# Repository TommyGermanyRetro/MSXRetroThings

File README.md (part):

# MSXRetroThings
<i>Some nerdy hard- and software for MSX machines</i>

When I was a child, my first computer was a <a href="https://www.msx.org/wiki/Category:SVI-3x8">SV 318 MKII</a> with a cassette recorder. But neither SPECTRON nor ARMOURED ASSAULT were my favourites - the expansion port and the table of its pins in the manual caught my full interest.

Unfortunately, I had no real clue how to connect those signals to my Z80 PIO in a way that worked, so I lost the fun of playing around with the hardware.

Now, 40 years later, I got a <a href="https://www.msx.org/wiki/Spectravideo_SVI-728">SVI 728</a> and a <a href="https://www.ebay.de/sch/i.html?item=332817640567&rt=nc&_trksid=p4429486.m145687.l2562&_ssn=fractal2000">memory mapper / SD card cartridge</a> from the bay, and also a <a href="https://www.8bits4ever.net/product-page/sxe-msx2-fpga-computer">SX-E MSX2+</a>, and started over.

I had a lot of chips in my basket like Z80 PIO, 8255, 8254, SJA1000, PCF8584 etc. It started with MSX cartridges, ROM code and <a href="https://rc2014.co.uk/">RC2014 cards</a> - and then one thing led to another:

- a real application on top of it: an MSX that joins a Maerklin model railway CAN bus as an accessory module,
- tools to bring old Spectravideo SVI-318/328 software back to life and over to MSX,
- my own emulators for the machines I grew up with and the ones I own now,
- a USB board that runs real MSX cartridges inside an emulator on the PC,
- the MSX1 picture on a PC screen, and a slot expander for more cartridges than slots.

Everything here is retro and nerdy stuff for your own developments - or just for gaming.

Some of the software comes from KONAMIMAN, especially the UNAPI structure and the memory allocation in BASIC for working areas in RAM. Please have a look at his <a href="https://www.konamiman.com/msx/msx-e.html">git</a> for further information.

Have fun and stay healthy,

Thomas

## Contents

| | Topic | In short |
| --- | --- | --- |
| 1 | [XIO cartridge](#1-msxretrothings---the-xio-cartridge) | switched IO, 8259 interrupt controller, IM2 emulation |
| 2 | [RCX ROM cartridge and RC2014 cards](#2-msxretrothings---the-rcx-rom-cartridge-and-rc2014-cards) | BASIC/UNAPI driver ROM for I2C/RTC, PIO, 8255, 8254, CAN, SPI, A/D, D/A cards |
| 3 | [mbc89](#3-msxretrothings---mbc89-a-maerklin-connect6021-can-accessory-module) | Maerklin Connect6021 CAN accessory module as an MSX-DOS 2 program |
| 4 | [Tools](#4-msxretrothings---tools) | SVI-3x8 TXT/CAS converter, CP/M disk builder, game porter to MSX |
| 5 | [Emulators](#5-msxretrothings---emulators) | SVI-318, SVI-328, SVI-728 and Philips VG-8235 |
| 6 | [USB2SLOT](#6-msxretrothings---usb2slot-real-msx-cartridges-in-openmsx) | real MSX cartridges in openMSX and the emulators above |
| 7 | [TMS9918A](#7-msxretrothings---tms9918a-the-msx1-picture-on-the-pc-screen) | the MSX1 picture on the PC screen |
| 8 | [Slot expander](#8-msxretrothings---slot-expander-four-cartridge-slots-for-one-msx-slot) | four cartridge slots for one MSX slot |
| 9 | [License](#9-license) | |

## 1. MSXRetroThings - The XIO cartridge

#### <b>1.1 The XIO cartridge contains these functions:</b>

+ Switched IO based on the idea of ASCII to achive 256 additional IO locations
+ 8 channel programable interrupt controller 8259 with fallen edge sensitive inputs
+ 8 channel daisy chain IM2 emulator
+ BASIC and UNAPI commands to controll the functionallities of the cartridge in on board BIOS ROM

#### <b>1.2 Impressions:</b>

XIO cartridge used in a SX-E MSX2+ with adapter to RC2014 backplane

XIO cartridge

Boot message from BIOS ROM

#### <b>1.3 Hardware:</b>

The schematics of XIO is strictly build up in non smd method to enable people without special tools to rebuild the pcb. But it uses GAL chips for the switched IO decoder, the glue decoder for controll signals and the address decoder.

PCB files: Eagle schematics and layouts, Gerber and drill files (also as zip for the PCB maker) and bills of materials of the XIO cartridge in [xio/pcb](xio/pcb) and of the RC2014 adapter in [rcx/rc2014_adapter/pcb](rcx/rc2014_adapter/pcb); GAL equations in [xio/gal](xio/gal).

The XIO OUT/IN functions work without installing the XIO card. If the XIO card is installed correctly, the green LED shows that alle 16 interrupt channels are ready to use. A blinking yellow LED shows activities to the switched IO addresses. It signals, that the switched IO is selected via &H40 of the original MSX IO bus. The red LED shows a working supply.

#### <b>1.4 Software:</b>

The BIOS for the card functions is provided in the on board ROM (EEPROM). It contains the additional BASIC commands and an instance of UNAPI.

For SDCC developments, a library was created as bridge to the ROM.

Command reference (syntax, parameters, UNAPI numbers, SDCC functions): [xio/README.md](xio/README.md#command-reference)

[↑ Contents](#contents)

## 2. MSXRetroThings - The RCX ROM cartridge and RC2014 cards

#### <b>2.1 The RCX ROM cartridge contains these functions:</b>

+ Up to 16 RC2014 cards installable with used IO address control and 16 bytes of free RAM each card

+ BASIC, SDCC and UNAPI commands to controll the functions of the cartridge in separate BIOS ROM cartridge

+ SDCC and UNAPI commands to controll the functions of the cartridge also avaiable as Driver for MSX-DOS 2

+ [RC2014 card with PCF8584 I2C Controller (3 ports via Seeed) and PCF8583 battery buffered RTC](#a-rc2014-card-with-pcf8584-i2c-controller-3-ports-via-seeed-and-pcf8583-battery-buffered-rtc)

+ [RC2014 card with SJA1000 CAN controller (single use only)](#e-rc2014-card-with-sja1000-can-controller-single-use-only)

+ [RC2014 card with 8255A PIO](#c-rc2014-card-with-8255a-pio)

+ [RC2014 card with 8254A CTR](#d-rc2014-card-with-8254a-ctr)

+ [RC2014 card with 4x SPI bus up to 2 MHz via ATMEGA8](#f-rc2014-card-with-4x-spi-bus-up-to-2-mhz-via-atmega8)

+ [RC2014 card with ADS1220 4 channel 24 bit A/D converter via ATMEGA8](#g-rc2014-card-with-ads1220-4-channel-24-bit-ad-converter-via-atmega8)

+ [RC2014 card with MCP4822 4 channel 12 bit D/A converter via ATMEGA8](#i-rc2014-card-with-mcp4822-4-channel-12-bit-da-converter-via-atmega8)

+ [RC2014 card SC103 with Z80 PIO](#b-rc2014-card-sc103-with-z80-pio)

+ [RC2014 card SC725 with Z80 SIO and Z80 CTC](#h-rc2014-card-sc725-with-z80-sio-and-z80-ctc)

The schematics of RC2014 cards are strictly build up in non smd method to enable people without special tools to rebuild the pcb.

#### <b>2.2 Impressions:</b>

Slot ROM

Boot message from BIOS ROM

#### <b>2.3 Hardware:</b>

PCB files: Eagle schematic and layout, Gerber and drill files (also as zip for the PCB maker) and bill of materials in [rcx/rc2014_rom+ram/pcb](rcx/rc2014_rom+ram/pcb).

#### <b>2.4 Software:</b>

The BIOS for the card functions is provided in the on board ROM (EEPROM). It contains the additional BASIC commands and an instance of UNAPI.

As a software-only alternative to the physical ROM cartridge, [`RCXRAM.COM`](rcx/rc2014_rom+ram/drv/RCXRAM.COM) installs the same `RCX_INTERFACE` UNAPI driver into mapped RAM at runtime instead of requiring a burned EEPROM - useful for testing and development without the actual cartridge. It is UNAPI/EXTBIOS-only (no BASIC `CALL` support, since that relies on BASIC's own boot-time scan of ROM header slots, which does not apply to a RAM segment). Covers all card types A through G and I.

For SDCC developments, a library was created as bridge to the ROM/DRV.

Command reference (syntax, parameters, UNAPI numbers, SDCC functions): [rcx/README.md](rcx/README.md#command-reference)

## A) RC2014 card with PCF8584 I2C Controller (3 ports via Seeed) and PCF8583 battery buffered RTC:

This RC2014 card contains an I2C bus controller PCF8584 and a PCF8583 RTC buffered by battery. The interrupt pins of both chips can be assigned to one of the XIO PIC interrupt channels.
Up to 16 cards of this type are possible.

#### <b>A.1 Impressions:</b>

RC2014 card on backplane

RC2014 card on backplane with I2C LCD from Seeed

RC2014 card on backplane contacted via BASIC to get TIME and DATE

#### <b>A.2 Hardware:</b>

PCB files: Eagle schematic and layout, Gerber and drill files (also as zip for the PCB maker) and bill of materials in [rcx/rc2014_card_a/pcb](rcx/rc2014_card_a/pcb).

#### <b>A.3 Software:</b>

The BIOS for the card functions is provided in the RCX slot ROM. It contains the additional BASIC commands (`I2C INIT/WR/WRB/RD/RDB/RESET`, `SET/GET TIME/DATE`) and an instance of UNAPI, so the same functions are callable directly via UNAPI/EXTBIOS from a `.COM` program without the BASIC interpreter. Test software exists both as interactive BASIC programs and as `.COM` tools, including a variant that keeps the SEED I2C LCD updated on every PIC interrupt and one that stays resident in memory (MemMan TSR) to keep updating the display in the background.

Command reference (syntax, parameters, UNAPI numbers, SDCC functions): [rcx/rc2014_card_a/README.md](rcx/rc2014_card_a/README.md#command-reference)

[↑ 2.1](#21-the-rcx-rom-cartridge-contains-these-functions)

## B) RC2014 card SC103 with Z80 PIO

The original RC2014 card SC103 from Small Computer Central: Z80 PIO with two 8-bit bidirectional ports A and B, each with two handshake lines. Port mode 0 (output), 1 (input), 2 (bidirectional, port A only) and 3 (bit control) are set by a raw control word. The IO base address is selectable (multiple of 4, 0...252), so several cards can be used side by side. Interrupts use the PIO's own IM2 vector through an XIO Z80 interrupt channel (8...15), so the XIO cartridge is needed for interrupt operation only.

#### <b>B.1 Impressions:</b>

RC2014 card on backplane

#### <b>B.2 Hardware:</b>

Original SC103 kit from Small Computer Central, no own PCB. The base address is set with the 6-way DIP switch SW1 (switches 1...6 = 128, 64, 32, 16, 8, 4; the address is the sum of the switches in the Off position); the card uses the base address and the next three addresses. Recommended by the manufacturer: `&H68` (second card `&H6C`). The ports are on P2 (2x13 pins, ribbon cable) and P3 (1x29 pins, Dupont). JP1/JP2 open: IEI/IEO only on P4, IEI pulled high on the card. Details: [rcx/rc2014_card_b/README.md](rcx/rc2014_card_b/README.md#hardware-setup).

#### <b>B.3 Software:</b>

The BIOS for the card functions is provided in the RCX slot ROM. It contains the additional BASIC commands (`PIO INIT`, `PIO A/B RD/WR`, `PIO A/B CTRL`) and an instance of UNAPI, so the same functions are callable directly via UNAPI/EXTBIOS from a `.COM` program without the BASIC interpreter. `PIO A/B CTRL` passes the Z80 PIO control word unchanged (mode, direction, interrupt vector, interrupt mask). The first test program writes Port A in mode 0 and reads Port B in mode 1. The second runs Port B in mode 3 with PB0 as interrupt input: the PIO puts its own IM2 vector on the bus (channel 0...7 → vector = channel * 2), and a small Z80 service routine registered through `XIO SET ADDR` (XIO channel 8...15) reports which channel fired. Both tests exist in BASIC, as `.COM` (`/IO:`, `/INT:`) and in C/SDCC; the `.COM` and SDCC programs also run with the RAM driver `RCXRAM.COM`.

Command reference (syntax, parameters, UNAPI numbers, SDCC functions): [rcx/rc2014_card_b/README.md](rcx/rc2014_card_b/README.md#command-reference)

[↑ 2.1](#21-the-rcx-rom-cartridge-contains-these-functions)

## C) RC2014 card with 8255A PIO

RC2014 card with a 8255 PIO. Up to 16 cards are possible. The interrupt pins of PORT C can be assigned to one of the XIO PIC interrupt channels.

#### <b>C.1 Impressions:</b>

RC2014 card on backplane

#### <b>C.2 Hardware:</b>

PCB files: Eagle schematic and layout, Gerber and drill files (also as zip for the PCB maker) and bill of materials in [rcx/rc2014_card_c/pcb](rcx/rc2014_card_c/pcb).

#### <b>C.3 Software:</b>

The BIOS for the card functions is provided in the RCX slot ROM. It contains the additional BASIC commands (`PPI INIT`, `PPI A/B/C RD/WR`, `PPI CTRL`, `PPI SET/RESET`) and an instance of UNAPI, so the same functions are callable directly via UNAPI/EXTBIOS from a `.COM` program without the BASIC interpreter. A second test program runs Port B in Mode 1 (strobed input), where the 82C55 itself raises `INTR B` on PC0 - reported through XIO's standard interrupt handler, no custom service routine needed.

Command reference (syntax, parameters, UNAPI numbers, SDCC functions): [rcx/rc2014_card_c/README.md](rcx/rc2014_card_c/README.md#command-reference)

[↑ 2.1](#21-the-rcx-rom-cartridge-contains-these-functions)

## D) RC2014 card with 8254A CTR

RC2014 card with a 8254 CTR. Up to 16 cards are possible. The interrupt pins of TIMER 0 and 1 can be assigned to one of the XIO PIC interrupt channels. This module does not work with internal clock if 8253 (max. 1 MHz) is used.

#### <b>D.1 Impressions:</b>

RC2014 card on backplane

#### <b>D.2 Hardware:</b>

PCB files: Eagle schematic and layout, Gerber and drill files (also as zip for the PCB maker) and bill of materials in [rcx/rc2014_card_d/pcb](rcx/rc2014_card_d/pcb).

#### <b>D.3 Software:</b>

The BIOS for the card functions is provided in the RCX slot ROM. It contains the additional BASIC commands (`TIMER INIT`, `TIMER 0/1/2 RD/WR`, `TIMER CTRL`, `TIMER SET/RESET GATE`) and an instance of UNAPI, so the same functions are callable directly via UNAPI/EXTBIOS from a `.COM` program without the BASIC interpreter. A second test program wires one of the counter outputs to a PIC interrupt channel and keeps a running interrupt count on screen.

Command reference (syntax, parameters, UNAPI numbers, SDCC functions): [rcx/rc2014_card_d/README.md](rcx/rc2014_card_d/README.md#command-reference)

[↑ 2.1](#21-the-rcx-rom-cartridge-contains-these-functions)

## E) RC2014 card with SJA1000 CAN controller (single use only)

RC2014 card with SJA1000 CAN controller and RJ45 sockets with automatic termination function. The software provides PELICAN Mode and 250 kBit/s.

Only one card is possible due to RAM allocation and interrupt handling. The interrupt pin of the SJA1000 can be assigned to one of the XIO PIC interrupt channels.

#### <b>E.1 Impressions:</b>

RC2014 card on backplane

#### <b>E.2 Hardware:</b>

PCB files: Eagle schematic and layout, Gerber and drill files (also as zip for the PCB maker) and bill of materials in [rcx/rc2014_card_e/pcb](rcx/rc2014_card_e/pcb).

#### <b>E.3 Software:</b>

The BIOS for the card functions is provided in the RCX slot ROM. It contains the additional BASIC commands (`CAN INIT`, `CAN WR/RD`, `CAN CHECK/RX/TX`, `CAN GET ADDR`) and an instance of UNAPI, so the same functions are callable directly via UNAPI/EXTBIOS from a `.COM` program without the BASIC interpreter. The test program receives and sends CAN messages interrupt-driven, e.g. for a Maerklin CS3 bus, by registering the ROM's own CAN service routine (returned by `CAN GET ADDR`) directly through `XIO SET ADDR` - no custom interrupt code needed.

Command reference (syntax, parameters, UNAPI numbers, SDCC functions): [rcx/rc2014_card_e/README.md](rcx/rc2014_card_e/README.md#command-reference)

[↑ 2.1](#21-the-rcx-rom-cartridge-contains-these-functions)

## F) RC2014 card with 4x SPI bus up to 2 MHz via ATMEGA8

RC2014 card with 4 SPI busses selectable via software with baudrate up to 2 MHz. Up to 16 SPI cards are possible. The interrupt pin of the ATMEGA8 can be assigned to one of the XIO PIC interrupt channels.

#### <b>F.1 Impressions:</b>

RC2014 card on backplane

#### <b>F.2 Hardware:</b>

PCB files: Eagle schematic and layout, Gerber and drill files (also as zip for the PCB maker) and bill of materials in [rcx/rc2014_card_f/pcb](rcx/rc2014_card_f/pcb).

#### <b>F.3 Software:</b>

The BIOS for the card functions is provided in the RCX slot ROM. It contains the additional BASIC commands (`SPI INIT/MODE`, `SPI WR/WRB/RD/RDB/RDH`) and an instance of UNAPI, so the same functions are callable directly via UNAPI/EXTBIOS from a `.COM` program without the BASIC interpreter. Up to 4 independent SPI busses are addressable per card; the test program exercises a MCP23S17 GPIO expander as a Port A/B loopback test.

Command reference (syntax, parameters, UNAPI numbers, SDCC functions): [rcx/rc2014_card_f/README.md](rcx/rc2014_card_f/README.md#command-reference)

[↑ 2.1](#21-the-rcx-rom-cartridge-contains-these-functions)

## G) RC2014 card with ADS1220 4 channel 24 bit A/D converter via ATMEGA8

RC2014 card with ADS1220 module. Up to 16 cards are possible. The interrupt pin of ATMEGA8 can be assigned to one of the XIO PIC interrupt channels.

#### <b>G.1 Impressions:</b>

RC2014 card on backplane

#### <b>G.2 Hardware:</b>

PCB files: Eagle schematic and layout, Gerber and drill files (also as zip for the PCB maker) and bill of materials in [rcx/rc2014_card_g/pcb](rcx/rc2014_card_g/pcb).

#### <b>G.3 Software:</b>

The BIOS for the card functions is provided in the RCX slot ROM. It contains the additional BASIC commands (`ADS INIT/MODE/CMD/STATUS/READ/GET`) and an instance of UNAPI, so the same functions are callable directly via UNAPI/EXTBIOS from a `.COM` program without the BASIC interpreter. `ADS GET` automates the whole measurement sequence (set MODE, start conversion, select channel, read all 4 RESULT bytes) into a single native `SNG` float value.

Command reference (syntax, parameters, UNAPI numbers, SDCC functions): [rcx/rc2014_card_g/README.md](rcx/rc2014_card_g/README.md#command-reference)

[↑ 2.1](#21-the-rcx-rom-cartridge-contains-these-functions)

## H) RC2014 card SC725 with Z80 SIO and Z80 CTC

The original RC2014 card SC725 from Small Computer Central as MSX COM port: Z80 SIO/2 with two serial ports, Z80 CTC as baud rate generator (110...19200 baud from the MSX bus clock). Port A and B become `COM0:` and `COM1:`. Interrupt driven receiving through the XIO Z80 interrupt channel 12, so the XIO cartridge is needed.

#### <b>H.1 Impressions:</b>

RC2014 card on backplane

#### <b>H.2 Hardware:</b>

Original SC725 kit from Small Computer Central, no own PCB. Jumpers for the MSX bus clock: JP4 1-2 (CTC clock = bus CLK), JP5 5-6 and JP6 5-6 (SIO A/B clock = CTC channel 0/1), JP1/JP2/JP3 open. Fixed IO addresses `&H80`...`&H83` (SIO) and `&H88`...`&H8B` (CTC). Details: [rcx/rc2014_card_h/README.md](rcx/rc2014_card_h/README.md#hardware-setup).

#### <b>H.3 Software:</b>

The BIOS for the card functions is provided in the RCX slot ROM. It contains an MSX RS-232C driver following the "RS-232C Extended BIOS Call Specification" (EXTBIO device 8, multi channel type), so any RS-232C aware MSX program finds the port. BASIC gets `_COM INIT`, the devices `COM0:`/`COM1:` (`OPEN`, `PRINT #`, `INPUT$`, `LOC`, `LOF`, `EOF`) and the CALL statements `COMINI`, `COMDTR`, `COMSTAT` and `COMBREAK`. CTS-RTS handshake, XON/XOFF, auto LF, SI/SO and break are supported. `.COM` and SDCC programs use the same driver via UNAPI/EXTBIOS, also with the RAM driver `RCXRAM.COM`.

Command reference (syntax, parameters, UNAPI numbers, SDCC functions): [rcx/rc2014_card_h/README.md](rcx/rc2014_card_h/README.md#command-reference)

[↑ 2.1](#21-the-rcx-rom-cartridge-contains-these-functions)

[↑ Contents](#contents)

## I) RC2014 card with MCP4822 4 channel 12 bit D/A converter via ATMEGA8

RC2014 card with 2x MCP4822. Up to 16 cards are possible. The interrupt pin of ATMEGA8 can be assigned to one of the XIO PIC interrupt channels.

#### <b>I.1 Impressions:</b>

RC2014 card on backplane

#### <b>I.2 Hardware:</b>

PCB files: Eagle schematic and layout, Gerber and drill files (also as zip for the PCB maker) and bill of materials in [rcx/rc2014_card_i/pcb](rcx/rc2014_card_i/pcb).

#### <b>I.3 Software:</b>

The BIOS for the card functions is provided in the RCX slot ROM. It contains the additional BASIC commands (`DAC INIT/SET/HOLD/CONF/GET`) and an instance of UNAPI, so the same functions are callable directly via UNAPI/EXTBIOS from a `.COM` program without the BASIC interpreter. Four outputs 0...4.095 V with 1 mV resolution; `DAC HOLD` and `DAC SET` together change several outputs at exactly the same moment.

Command reference (syntax, parameters, UNAPI numbers, SDCC functions): [rcx/rc2014_card_i/README.md](rcx/rc2014_card_i/README.md#command-reference)

[↑ 2.1](#21-the-rcx-rom-cartridge-contains-these-functions)

[↑ Contents](#contents)

## 3. MSXRetroThings - mbc89, a Maerklin Connect6021 CAN accessory module

#### <b>3.1 mbc89 provides:</b>

+ A full MSX-DOS 2 port of `mbc89`, one of the MBCAN family of Maerklin CS2/CS3 CAN-bus accessory modules - runs as a normal `.COM` program instead of the original's ATmega firmware

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
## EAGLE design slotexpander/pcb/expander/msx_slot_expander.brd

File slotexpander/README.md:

# Slot expander - four cartridge slots for one MSX slot

A slot expander for MSX computers: four cartridge slots behind one primary slot, as subslots 0-3 of
a standard MSX slot expander with its register at FFFFh. It sits outside the computer on a 50-wire
ribbon cable and has its own 5 V supply, so the cartridges in it do not load the power supply of the
MSX.

The expander connects to the MSX in one of two ways:

- **Spectravideo SVI-728:** the 50-pin box header of the expander follows the pinout of the
  SVI-728, so the ribbon cable goes straight to the SVI-728.
- **Any other MSX:** plug the Slot2Bus adapter into a cartridge slot. It takes the 50 contacts of
  the slot 1:1 to its box header, and the ribbon cable goes from there to the expander.

Tested on a Spectravideo SVI-728.

## Contents of this folder

| Path | Content |
| --- | --- |
| [pcb/expander](pcb/expander) | Eagle project of the expander: schematic `msx_slot_expander.sch`, layout `msx_slot_expander.brd`; bill of materials `msx_slot_expander_bom.csv` |
| [pcb/expander/gerber](pcb/expander/gerber) | Gerber RS-274X and Excellon drill files of the two-layer board, also as `msx_slot_expander_gerber.zip` for the PCB maker |
| [pcb/adapter](pcb/adapter) | Eagle project of the Slot2Bus adapter: `msx_slot2bus_expander.sch`, `msx_slot2bus_expander.brd`; bill of materials `msx_slot2bus_expander_bom.csv` |
| [pcb/adapter/gerber](pcb/adapter/gerber) | Gerber and drill files of the adapter, also as `msx_slot2bus_expander_gerber.zip` |
| [gal](gal) | GAL equations (WinCUPL) and programming files: `FPGA_EXP_ADR_BANKING` (GAL22V10), `FPGA_EXP_IO_CTRL` (GAL16V8) |
| [case](case) | 3D-printable enclosures as FreeCAD files: expander `MSX_EXPANDER_BOTTOM/TOP.FCStd`, adapter `MSX_CARD_SLOT2BUS_BOTTOM/TOP.FCStd` |
| [media](media) | Photo |

## 1. How it works

| Function | Implementation |
| --- | --- |
| Subslot register FFFFh | Two 74HCT30 detect the address FFFFh. The GAL22V10 `FPGA_EXP_ADR_BANKING` stores the value written to FFFFh while the slot is selected and returns it inverted on a read, as the MSX standard requires. |
| Subslot select | For each memory access, the GAL22V10 picks the two register bits of the page given by A15/A14. The GAL16V8 `FPGA_EXP_IO_CTRL` turns them into /SLTSL of subslot 0-3; accesses to FFFFh itself do not select a subslot. |
| Subslots on and off | DIP switch S101 connects each subslot select to its slot. Open, the subslot stays empty for the MSX. |
| /INT and /BUSDIR | Each slot reaches the line of the MSX through a diode, with a pull-up on the expander. |
| Sound | The sound output of each slot goes through its own 10 kOhm trimmer to the sound input of the MSX, so the level of each cartridge can be set. |
| Power | 5 V through a USB type B socket, a ferrite bead and the power switch; +12 V and -12 V for the slots from a DC-DC converter NMA0512. The 5 V of the MSX only light the LED "MSX". |

| LED | Meaning |
| --- | --- |
| MSX | the MSX is switched on (5 V on the ribbon cable) |
| EXP | the expander is switched on |

## 2. Hardware

- Order the boards with the zip files in `pcb/expander/gerber` and `pcb/adapter/gerber`. Check the
  layers in a Gerber viewer (for example the online viewer of the PCB maker) before you order. The
  parts are listed in the two bill-of-materials files.
- Program the GALs with `gal/FPGA_EXP_ADR_BANKING.jed` (GAL22V10) and `gal/FPGA_EXP_IO_CTRL.jed`
  (GAL16V8).
- The two LEDs have no series resistor on the board; use LEDs with a built-in resistor for 5 V.
- The ribbon cable has 50 wires with an IDC socket at each end. Mind pin 1 at both ends.
- Supply: a USB power supply with 5 V and enough current for the cartridges plugged in. The
  cartridges are powered by the expander, not by the MSX: with the expander switched off, they do not
  work.
- Switch on the expander first, then the MSX.
- No hot plug, just like a real MSX: change cartridges only with the expander and the MSX switched
  off.

## 3. Enclosures

`case` holds two-part enclosures as FreeCAD files, built with FreeCAD 1.0 (PartDesign):

| Files | Part | Size (outside) |
| --- | --- | --- |
| `MSX_EXPANDER_BOTTOM.FCStd`, `MSX_EXPANDER_TOP.FCStd` | expander | 150 x 115 mm; bottom part 10 mm, top part 30 mm high |
| `MSX_CARD_SLOT2BUS_BOTTOM.FCStd`, `MSX_CARD_SLOT2BUS_TOP.FCStd` | Slot2Bus adapter, cartridge shaped | 111 x 68 mm; bottom part 11 mm, top part 15 mm high |

Only the design files are included, no STL or G-code, so the enclosures can be adapted before
printing:

1. Open the files in FreeCAD 1.0 or newer and change the sketches as needed; the following features
   update automatically.
2. Select the body and export it as STL or 3MF (File > Export).
3. Slice the file for your printer as usual.

## 4. License

The parts in this folder follow the [license of this repository](../README.md#9-license): the
boards, the GAL equations and the enclosures CERN-OHL-S-2.0, documentation and photo CC BY-SA 4.0.

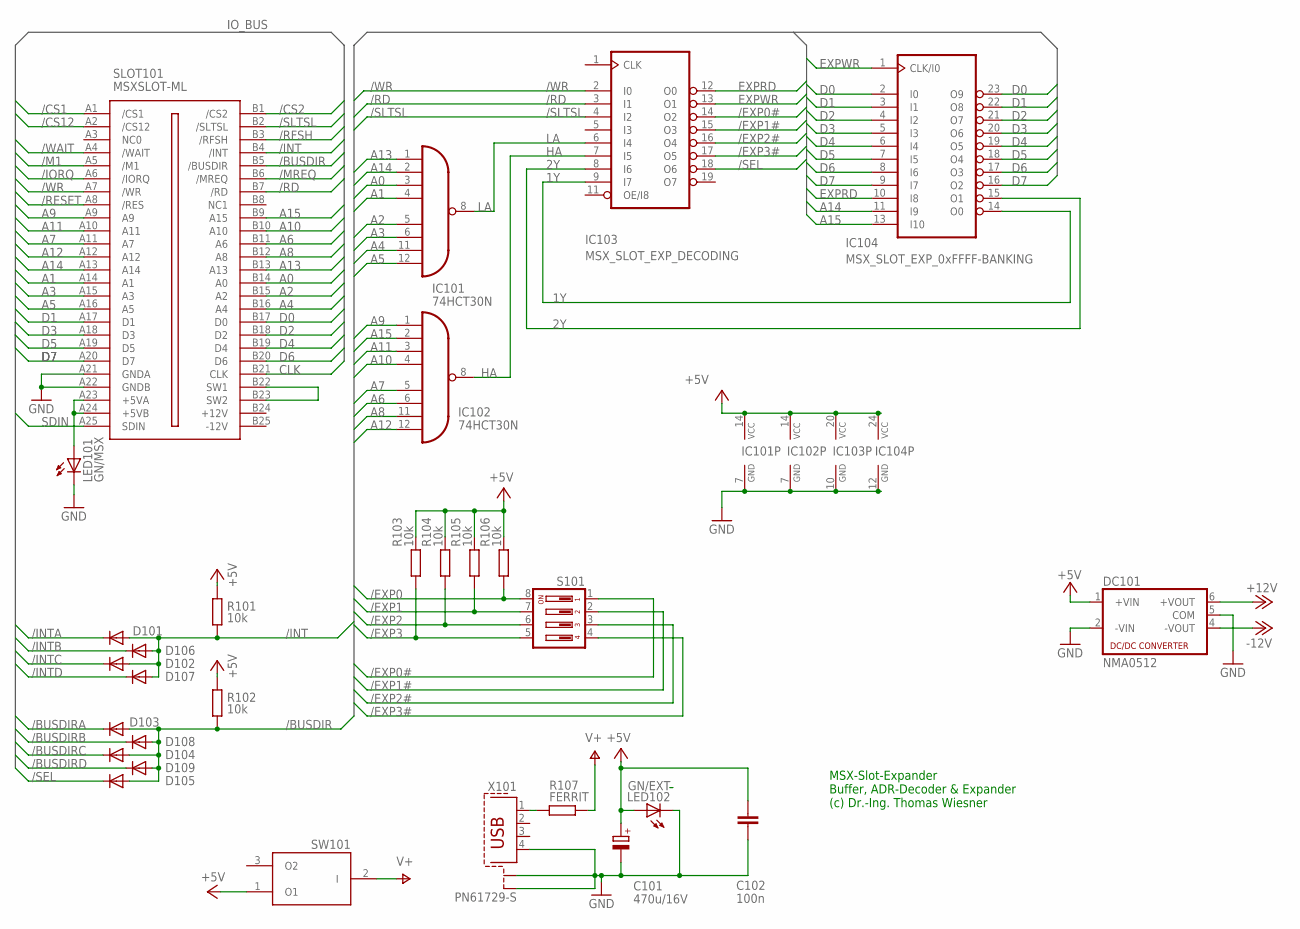
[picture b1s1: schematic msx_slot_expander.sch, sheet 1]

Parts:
C101: 470u/16V; E3,5-8
C102: 100n; C025-025X050
D101, D102, D103, D104, D105, D106, D107, D108, D109: 1N4148; DO35-10
DC101: NMA0512; NMA
IC101, IC102: 74HCT30N; DIL14
IC103: MSX_SLOT_EXP_DECODING; DIL20
IC104: MSX_SLOT_EXP_0xFFFF-BANKING; DIL24-3
LED101: GN/MSX; LED3MM
LED102: GN/EXT; LED3MM
R101, R102, R103, R104, R105, R106: 10k; 0207/10
R107: FERRIT; 0207/10
S101: DA04; DA-04
SLOT101: MSXSLOT-ML
SW101: TS-13PA; TS-13-P
X101: PN61729-S

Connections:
1Y: IC103.9 (I7), IC104.14 (O0)
2Y: IC103.8 (I6), IC104.15 (O1)
+5V: C101.+, C102.2, DC101.1 (+VIN), IC101.14 (VCC), IC102.14 (VCC), IC103.20 (VCC), IC104.24 (VCC), LED102.A, R101.2, R102.1, R103.2, R104.2, R105.2, R106.2, SW101.1 (O1); also elsewhere on the board
+12V: DC101.6 (+VOUT); also elsewhere on the board
-12V: DC101.4 (-VOUT); also elsewhere on the board
/BUSDIR: D103.A, D104.A, D105.A, D108.A, D109.A, R102.2, SLOT101.B5 (/BUSDIR)
/BUSDIRA: D103.C; also elsewhere on the board
/BUSDIRB: D108.C; also elsewhere on the board
/BUSDIRC: D104.C; also elsewhere on the board
/BUSDIRD: D109.C; also elsewhere on the board
/CS1: SLOT101.A1 (/CS1); also elsewhere on the board
/CS2: SLOT101.B1 (/CS2); also elsewhere on the board
/CS12: SLOT101.A2 (/CS12); also elsewhere on the board
/EXP0: R106.1, S101.8; also elsewhere on the board
/EXP0#: IC103.14 (O2), S101.1
/EXP1: R105.1, S101.7; also elsewhere on the board
/EXP1#: IC103.15 (O3), S101.2
/EXP2: R104.1, S101.6; also elsewhere on the board
/EXP2#: IC103.16 (O4), S101.3
/EXP3: R103.1, S101.5; also elsewhere on the board
/EXP3#: IC103.17 (O5), S101.4
/INT: D101.A, D102.A, D106.A, D107.A, R101.1, SLOT101.B4 (/INT)
/INTA: D101.C; also elsewhere on the board
/INTB: D106.C; also elsewhere on the board
/INTC: D102.C; also elsewhere on the board
/INTD: D107.C; also elsewhere on the board
/IORQ: SLOT101.A6 (/IORQ); also elsewhere on the board
/M1: SLOT101.A5 (/M1); also elsewhere on the board
/MREQ: SLOT101.B6 (/MREQ); also elsewhere on the board
/RD: IC103.3 (I1), SLOT101.B7 (/RD); also elsewhere on the board
/RESET: SLOT101.A8 (/RES); also elsewhere on the board
/RFSH: SLOT101.B3 (/RFSH); also elsewhere on the board
/SEL: D105.C, IC103.18 (O6)
/SLTSL: IC103.4 (I2), SLOT101.B2 (/SLTSL)
/WAIT: SLOT101.A4 (/WAIT); also elsewhere on the board
/WR: IC103.2 (I0), SLOT101.A7 (/WR); also elsewhere on the board
A0: IC101.3 (I2), SLOT101.B14 (A0); also elsewhere on the board
A1: IC101.4 (I3), SLOT101.A14 (A1); also elsewhere on the board
A2: IC101.5 (I4), SLOT101.B15 (A2); also elsewhere on the board
A3: IC101.6 (I5), SLOT101.A15 (A3); also elsewhere on the board
A4: IC101.11 (I6), SLOT101.B16 (A4); also elsewhere on the board
A5: IC101.12 (I7), SLOT101.A16 (A5); also elsewhere on the board
A6: IC102.6 (I5), SLOT101.B11 (A6); also elsewhere on the board
A7: IC102.5 (I4), SLOT101.A11 (A7); also elsewhere on the board
A8: IC102.11 (I6), SLOT101.B12 (A8); also elsewhere on the board
A9: IC102.1 (I0), SLOT101.A9; also elsewhere on the board
A10: IC102.4 (I3), SLOT101.B10 (A10); also elsewhere on the board
A11: IC102.3 (I2), SLOT101.A10 (A11); also elsewhere on the board
A12: IC102.12 (I7), SLOT101.A12; also elsewhere on the board
A13: IC101.1 (I0), SLOT101.B13 (A13); also elsewhere on the board
A14: IC101.2 (I1), IC104.11 (I9), SLOT101.A13 (A14); also elsewhere on the board
A15: IC102.2 (I1), IC104.13 (I10), SLOT101.B9 (A15); also elsewhere on the board
CLK: SLOT101.B21 (CLK); also elsewhere on the board
D0: IC104.2 (I0), IC104.23 (O9), SLOT101.B17 (D0); also elsewhere on the board
D1: IC104.3 (I1), IC104.22 (O8), SLOT101.A17 (D1); also elsewhere on the board
D2: IC104.4 (I2), IC104.21 (O7), SLOT101.B18 (D2); also elsewhere on the board
D3: IC104.5 (I3), IC104.20 (O6), SLOT101.A18 (D3); also elsewhere on the board
D4: IC104.6 (I4), IC104.19 (O5), SLOT101.B19 (D4); also elsewhere on the board
D5: IC104.7 (I5), IC104.18 (O4), SLOT101.A19 (D5); also elsewhere on the board
D6: IC104.8 (I6), IC104.17 (O3), SLOT101.B20 (D6); also elsewhere on the board
D7: IC104.9 (I7), IC104.16 (O2), SLOT101.A20 (D7); also elsewhere on the board
EXPRD: IC103.12 (O0), IC104.10 (I8)
EXPWR: IC103.13 (O1), IC104.1 (CLK/I0)
GND: C101.-, C102.1, DC101.2 (-VIN), DC101.5 (COM), IC101.7 (GND), IC102.7 (GND), IC103.10 (GND), IC104.12 (GND), LED101.K (C), LED102.K (C), SLOT101.A21 (GNDA), SLOT101.A22 (GNDB), X101.4, X101.S1, X101.S2; also elsewhere on the board
HA: IC102.8 (O), IC103.7 (I5)
LA: IC101.8 (O), IC103.6 (I4)
unnamed: LED101.A, SLOT101.A23 (+5VA), SLOT101.A24 (+5VB)
unnamed: R107.2, X101.1
unnamed: SLOT101.B22 (SW1), SLOT101.B23 (SW2)
SDIN: SLOT101.A25 (SDIN); also elsewhere on the board
V+: R107.1, SW101.2 (I)

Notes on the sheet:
MSX-Slot-Expander Buffer, ADR-Decoder & Expander (c) Dr.-Ing. Thomas Wiesner

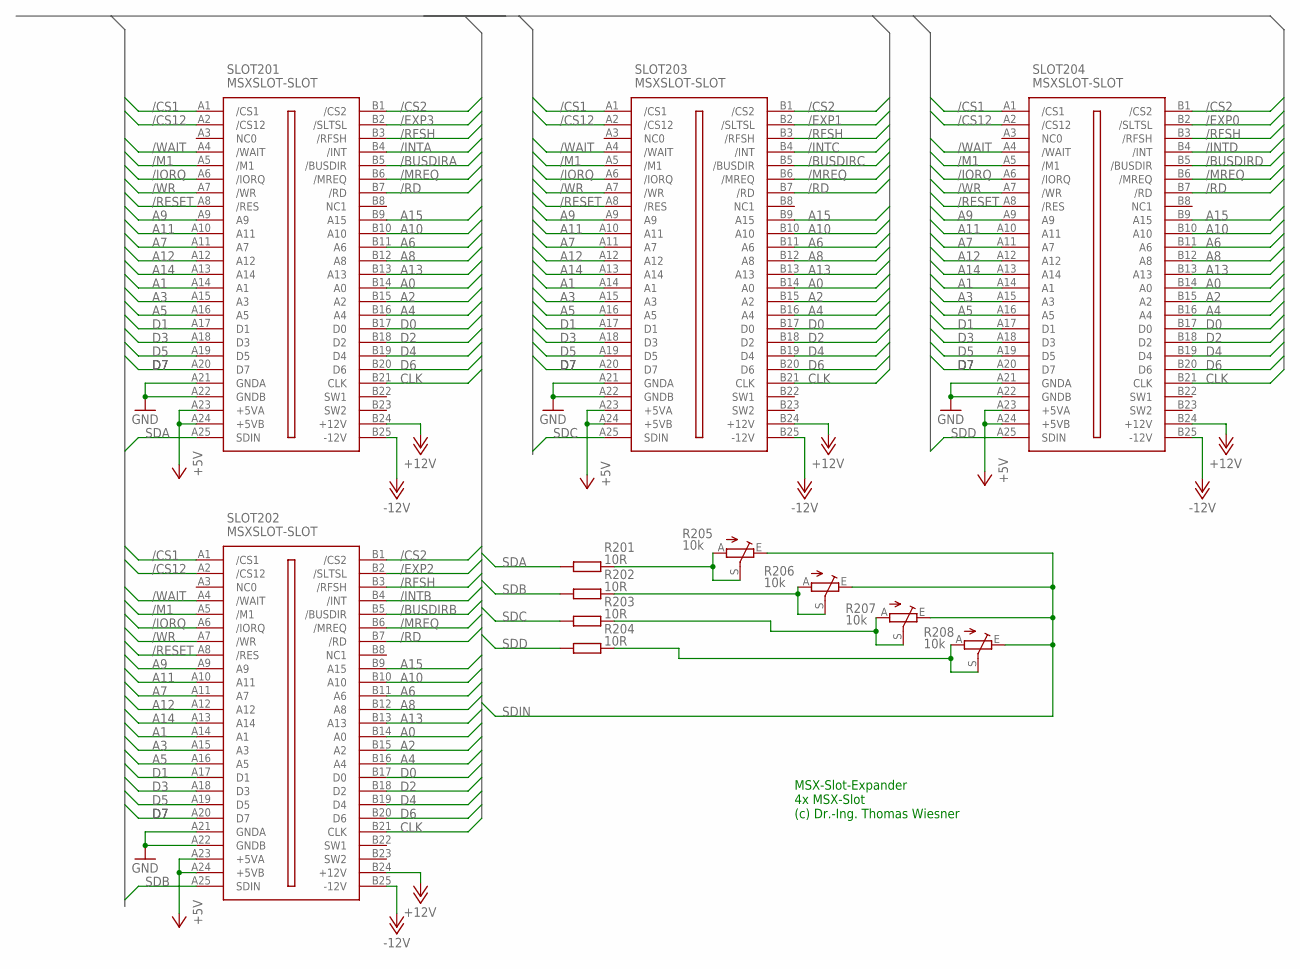
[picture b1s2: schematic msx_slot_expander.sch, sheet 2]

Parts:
R201, R202, R203, R204: 10R; 0207/10
R205, R206, R207, R208: 10k; SP19L
SLOT201, SLOT202, SLOT203, SLOT204: MSXSLOT-SLOT; MSXSLOT

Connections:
+5V: SLOT201.A23 (+5VA), SLOT201.A24 (+5VB), SLOT202.A23 (+5VA), SLOT202.A24 (+5VB), SLOT203.A23 (+5VA), SLOT203.A24 (+5VB), SLOT204.A23 (+5VA), SLOT204.A24 (+5VB); also elsewhere on the board
+12V: SLOT201.B24 (+12V), SLOT202.B24 (+12V), SLOT203.B24 (+12V), SLOT204.B24 (+12V); also elsewhere on the board
-12V: SLOT201.B25 (-12V), SLOT202.B25 (-12V), SLOT203.B25 (-12V), SLOT204.B25 (-12V); also elsewhere on the board
/BUSDIRA: SLOT201.B5 (/BUSDIR); also elsewhere on the board
/BUSDIRB: SLOT202.B5 (/BUSDIR); also elsewhere on the board
/BUSDIRC: SLOT203.B5 (/BUSDIR); also elsewhere on the board
/BUSDIRD: SLOT204.B5 (/BUSDIR); also elsewhere on the board
/CS1: SLOT201.A1 (/CS1), SLOT202.A1 (/CS1), SLOT203.A1 (/CS1), SLOT204.A1 (/CS1); also elsewhere on the board
/CS2: SLOT201.B1 (/CS2), SLOT202.B1 (/CS2), SLOT203.B1 (/CS2), SLOT204.B1 (/CS2); also elsewhere on the board
/CS12: SLOT201.A2 (/CS12), SLOT202.A2 (/CS12), SLOT203.A2 (/CS12), SLOT204.A2 (/CS12); also elsewhere on the board
/EXP0: SLOT204.B2 (/SLTSL); also elsewhere on the board
/EXP1: SLOT203.B2 (/SLTSL); also elsewhere on the board
/EXP2: SLOT202.B2 (/SLTSL); also elsewhere on the board
/EXP3: SLOT201.B2 (/SLTSL); also elsewhere on the board
/INTA: SLOT201.B4 (/INT); also elsewhere on the board
/INTB: SLOT202.B4 (/INT); also elsewhere on the board
/INTC: SLOT203.B4 (/INT); also elsewhere on the board
/INTD: SLOT204.B4 (/INT); also elsewhere on the board
/IORQ: SLOT201.A6 (/IORQ), SLOT202.A6 (/IORQ), SLOT203.A6 (/IORQ), SLOT204.A6 (/IORQ); also elsewhere on the board
/M1: SLOT201.A5 (/M1), SLOT202.A5 (/M1), SLOT203.A5 (/M1), SLOT204.A5 (/M1); also elsewhere on the board
/MREQ: SLOT201.B6 (/MREQ), SLOT202.B6 (/MREQ), SLOT203.B6 (/MREQ), SLOT204.B6 (/MREQ); also elsewhere on the board
/RD: SLOT201.B7 (/RD), SLOT202.B7 (/RD), SLOT203.B7 (/RD), SLOT204.B7 (/RD); also elsewhere on the board
/RESET: SLOT201.A8 (/RES), SLOT202.A8 (/RES), SLOT203.A8 (/RES), SLOT204.A8 (/RES); also elsewhere on the board
/RFSH: SLOT201.B3 (/RFSH), SLOT202.B3 (/RFSH), SLOT203.B3 (/RFSH), SLOT204.B3 (/RFSH); also elsewhere on the board
/WAIT: SLOT201.A4 (/WAIT), SLOT202.A4 (/WAIT), SLOT203.A4 (/WAIT), SLOT204.A4 (/WAIT); also elsewhere on the board
/WR: SLOT201.A7 (/WR), SLOT202.A7 (/WR), SLOT203.A7 (/WR), SLOT204.A7 (/WR); also elsewhere on the board
A0: SLOT201.B14 (A0), SLOT202.B14 (A0), SLOT203.B14 (A0), SLOT204.B14 (A0); also elsewhere on the board
A1: SLOT201.A14 (A1), SLOT202.A14 (A1), SLOT203.A14 (A1), SLOT204.A14 (A1); also elsewhere on the board
A2: SLOT201.B15 (A2), SLOT202.B15 (A2), SLOT203.B15 (A2), SLOT204.B15 (A2); also elsewhere on the board
A3: SLOT201.A15 (A3), SLOT202.A15 (A3), SLOT203.A15 (A3), SLOT204.A15 (A3); also elsewhere on the board
A4: SLOT201.B16 (A4), SLOT202.B16 (A4), SLOT203.B16 (A4), SLOT204.B16 (A4); also elsewhere on the board
A5: SLOT201.A16 (A5), SLOT202.A16 (A5), SLOT203.A16 (A5), SLOT204.A16 (A5); also elsewhere on the board
A6: SLOT201.B11 (A6), SLOT202.B11 (A6), SLOT203.B11 (A6), SLOT204.B11 (A6); also elsewhere on the board
A7: SLOT201.A11 (A7), SLOT202.A11 (A7), SLOT203.A11 (A7), SLOT204.A11 (A7); also elsewhere on the board
A8: SLOT201.B12 (A8), SLOT202.B12 (A8), SLOT203.B12 (A8), SLOT204.B12 (A8); also elsewhere on the board
A9: SLOT201.A9, SLOT202.A9, SLOT203.A9, SLOT204.A9; also elsewhere on the board
A10: SLOT201.B10 (A10), SLOT202.B10 (A10), SLOT203.B10 (A10), SLOT204.B10 (A10); also elsewhere on the board
A11: SLOT201.A10 (A11), SLOT202.A10 (A11), SLOT203.A10 (A11), SLOT204.A10 (A11); also elsewhere on the board
A12: SLOT201.A12, SLOT202.A12, SLOT203.A12, SLOT204.A12; also elsewhere on the board
A13: SLOT201.B13 (A13), SLOT202.B13 (A13), SLOT203.B13 (A13), SLOT204.B13 (A13); also elsewhere on the board
A14: SLOT201.A13 (A14), SLOT202.A13 (A14), SLOT203.A13 (A14), SLOT204.A13 (A14); also elsewhere on the board
A15: SLOT201.B9 (A15), SLOT202.B9 (A15), SLOT203.B9 (A15), SLOT204.B9 (A15); also elsewhere on the board
CLK: SLOT201.B21 (CLK), SLOT202.B21 (CLK), SLOT203.B21 (CLK), SLOT204.B21 (CLK); also elsewhere on the board
D0: SLOT201.B17 (D0), SLOT202.B17 (D0), SLOT203.B17 (D0), SLOT204.B17 (D0); also elsewhere on the board
D1: SLOT201.A17 (D1), SLOT202.A17 (D1), SLOT203.A17 (D1), SLOT204.A17 (D1); also elsewhere on the board
D2: SLOT201.B18 (D2), SLOT202.B18 (D2), SLOT203.B18 (D2), SLOT204.B18 (D2); also elsewhere on the board
D3: SLOT201.A18 (D3), SLOT202.A18 (D3), SLOT203.A18 (D3), SLOT204.A18 (D3); also elsewhere on the board
D4: SLOT201.B19 (D4), SLOT202.B19 (D4), SLOT203.B19 (D4), SLOT204.B19 (D4); also elsewhere on the board
D5: SLOT201.A19 (D5), SLOT202.A19 (D5), SLOT203.A19 (D5), SLOT204.A19 (D5); also elsewhere on the board
D6: SLOT201.B20 (D6), SLOT202.B20 (D6), SLOT203.B20 (D6), SLOT204.B20 (D6); also elsewhere on the board
D7: SLOT201.A20 (D7), SLOT202.A20 (D7), SLOT203.A20 (D7), SLOT204.A20 (D7); also elsewhere on the board
GND: SLOT201.A21 (GNDA), SLOT201.A22 (GNDB), SLOT202.A21 (GNDA), SLOT202.A22 (GNDB), SLOT203.A21 (GNDA), SLOT203.A22 (GNDB), SLOT204.A21 (GNDA), SLOT204.A22 (GNDB); also elsewhere on the board
unnamed: R201.2, R205.A, R205.S
unnamed: R202.2, R206.A, R206.S
unnamed: R203.2, R207.A, R207.S
unnamed: R204.2, R208.A, R208.S
SDA: R201.1, SLOT201.A25 (SDIN)
SDB: R202.1, SLOT202.A25 (SDIN)
SDC: R203.1, SLOT203.A25 (SDIN)
SDD: R204.1, SLOT204.A25 (SDIN)
SDIN: R205.E, R206.E, R207.E, R208.E; also elsewhere on the board

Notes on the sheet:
MSX-Slot-Expander 4x MSX-Slot (c) Dr.-Ing. Thomas Wiesner

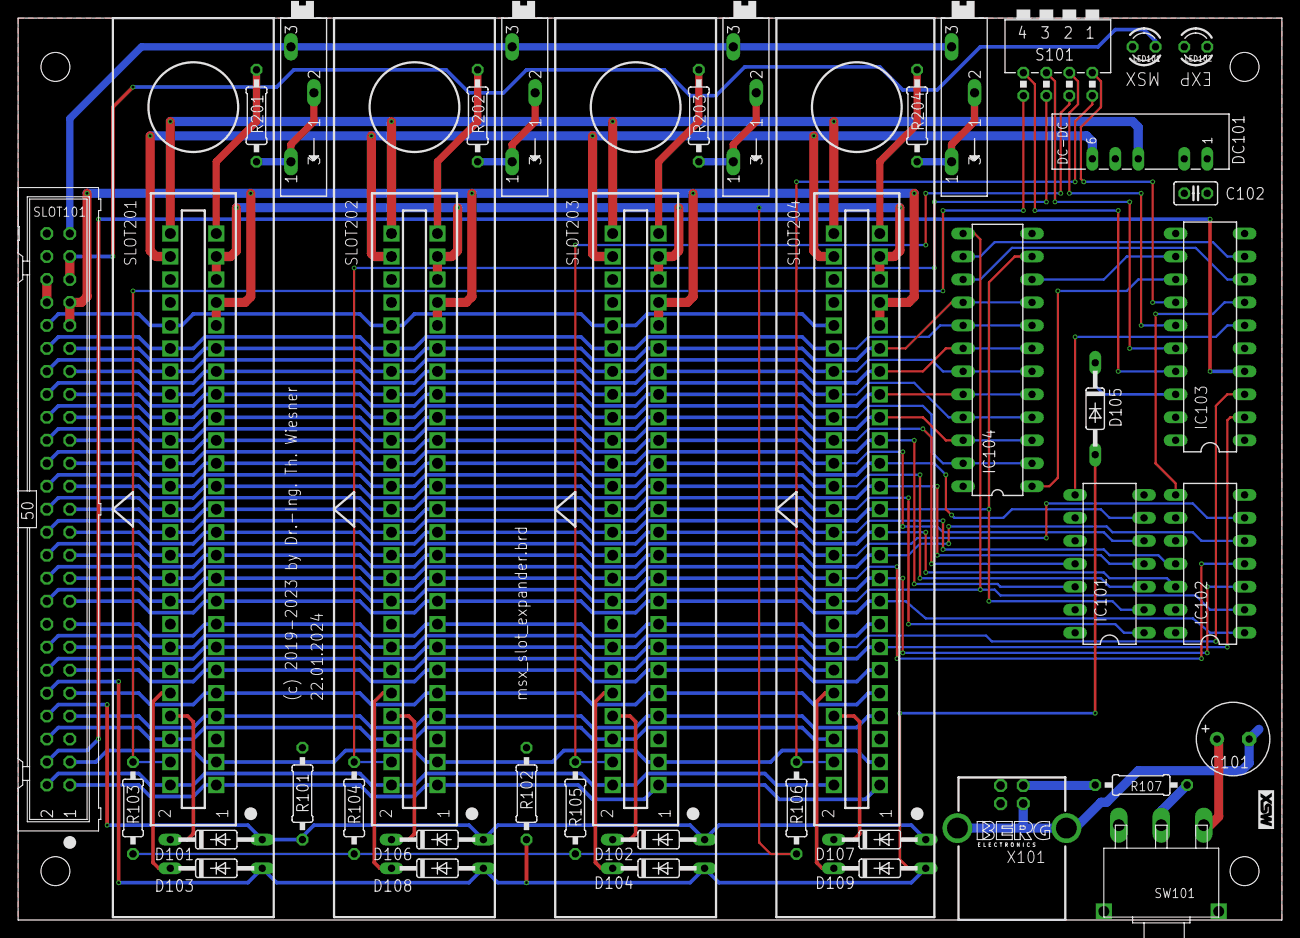
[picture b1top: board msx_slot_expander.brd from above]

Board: 2 copper layers, 139.7 x 99.7 mm, 41 parts (0 on the bottom side), 79 nets.

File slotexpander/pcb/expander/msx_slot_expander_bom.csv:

Qty,Reference,Value,Package,Description
4,"SLOT201, SLOT202, SLOT203, SLOT204",MSX slot,MSXSLOT,"MSX cartridge slot, 50 pins (2 x 25), 2.54 mm pitch"
1,SLOT101,Box header 2x25,MSXSLOT-ML,"Box header 50 pins (2 x 25), 2.54 mm, for the ribbon cable to the MSX"
1,IC104,GAL22V10,DIL24-3,"GAL22V10, programmed with gal/FPGA_EXP_ADR_BANKING.jed: subslot register FFFFh"
1,IC103,GAL16V8,DIL20,"GAL16V8, programmed with gal/FPGA_EXP_IO_CTRL.jed: subslot selects /EXP0-/EXP3"
2,"IC101, IC102",74HCT30N,DIL14,"8-input NAND, together they detect address FFFFh (IC101 A0-A5, A13, A14; IC102 A6-A12, A15)"
1,DC101,NMA0512,NMA,"DC-DC converter 5 V to +12 V / -12 V (Murata NMA0512SC) for the slots"
1,X101,PN61729-S,PN61729-S,"USB type B socket (FCI/Berg PN61729-S), 5 V power input"
1,SW101,TS-13P,TS-13-P,Power switch
1,R107,Ferrite bead,0207/10,"Ferrite bead in the 5 V input, axial, 10 mm pitch"
1,S101,DIP switch 4x,DA-04,"DIP switch, 4 positions: connects subslot 0-3"
9,"D101, D102, D103, D104, D105, D106, D107, D108, D109",1N4148,DO35-10,"Signal diode: /INT and /BUSDIR of the slots to the MSX"
6,"R101, R102, R103, R104, R105, R106",10k,0207/10,"Resistor 10 kOhm, axial, 10 mm pitch: pull-ups /INT, /BUSDIR, /EXP0-/EXP3"
4,"R201, R202, R203, R204",10R,0207/10,"Resistor 10 Ohm, axial, 10 mm pitch, in the sound input of each slot"
4,"R205, R206, R207, R208",10k,SP19L,"Trimmer potentiometer 10 kOhm: sound level of each slot"
2,"LED101, LED102",GR-5V,LED3MM,"LED 3 mm green with built-in resistor for 5 V (LED101 MSX powered, LED102 expander powered)"
1,C101,470u/16V,E3.5-8,"Electrolytic capacitor 470 uF 16 V, radial, 3.5 mm pitch, 8 mm diameter"
1,C102,100n,C025-025X050,"Ceramic capacitor 100 nF, 2.5 mm pitch"
1,-,Ribbon cable,-,"Ribbon cable 50 wires with two IDC sockets 2 x 25, 2.54 mm (to the SVI-728 or to the Slot2Bus adapter)"

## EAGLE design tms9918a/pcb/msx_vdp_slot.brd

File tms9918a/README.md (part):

# TMS9918A - the MSX1 picture on the PC screen

A small debugging card for a cartridge slot of a real MSX1 and a passive, exact emulation of its
video display processor (VDP), the TI TMS9918A, on a Windows PC. It was made for development work:
instead of a second monitor or an old CRT on the desk, the picture of the real MSX appears in a
window on the PC, sharp and flicker-free, next to the editor, the assembler and the other tools on
the same screen.

The emulator does not run any MSX software itself. A Raspberry Pi Pico on the card listens to every
access of the Z80 to the VDP (ports 98h/99h) and sends it to the PC over USB. The emulator replays
these accesses on its own TMS9918A model and shows the resulting picture. The MSX keeps running at
full speed with its own VDP; the card only listens.

Because the Pico also captures the values the real VDP returns on reads (VRAM data and status
register), every read checks the model against the real chip. The status display counts and logs all
mismatches, so the emulation is measurable rather than just "looks right".

```text
 MSX (Z80 + real VDP)          Raspberry Pi Pico               PC
 ports 98h/99h  ── slot ──►  PIO capture, time stamps  ── USB ──►  TMS9918A emulator
                ◄─ /RES ───  reset on request          ◄─ "7" ───  (VB.NET, Windows)
```

Tested on a Spectravideo SVI-728 (TMS9929A, PAL) with MSX BASIC, Nextor, SofaRun and games: no
mismatches in VRAM reads and status reads.

**Video: an SVI-728 from power-on to GALAGA.** Recorded with the video recording of the emulator:
the start with the SD card driver of the cartridge, Nextor, SofaRun and a round of GALAGA. Nothing
of it comes from the video output of the MSX; every picture is rebuilt from the VDP accesses the
card has captured. Click the picture to open the video.

## Contents of this folder

| Path | Content |
| --- | --- |
| [bin](bin) | Ready-to-run emulator for Windows x64: `TMS9918A.exe` with `TMS9918AVideo.dll` |
| [TMS9918A](TMS9918A) | Emulator source, Visual Basic .NET (Windows Forms, .NET Framework 4.5) |
| [TMS9918AVideo](TMS9918AVideo) | Native DLL (C++, x64) for the video recording, built on [emu/chips/VIDEOREC](../emu/chips/VIDEOREC) |
| `TMS9918A.sln` | Visual Studio solution |
| [TMS9918aPiPico](TMS9918aPiPico) | Raspberry Pi Pico firmware (Arduino-Pico core, PIO), see its [README](TMS9918aPiPico/README.md) |
| `TMS9918aPiPico.ino.uf2` | Ready-to-flash firmware |
| [pcb](pcb) | Eagle project of the card: schematic `msx_vdp_slot.sch`, layout `msx_vdp_slot.brd`; bill of materials `msx_vdp_slot_bom.csv`; photos |
| [pcb/gerber](pcb/gerber) | Gerber RS-274X and Excellon drill files of the two-layer board, also as `msx_vdp_slot_gerber.zip` for the PCB maker |
| [pcb/gal](pcb/gal) | GAL22V10 equations `FPGA_IO.PLD` (WinCUPL) and the programming file `FPGA_IO.jed` |
| [media](media) | Video: an SVI-728 from power-on to GALAGA |
| [DATA_FORMATS.md](DATA_FORMATS.md) | USB protocol, synchronisation, VDP ports, registers and the comparison rules |

Main source files of the emulator:

| File | Content |
| --- | --- |
| `clVDP.vb` | TMS9918A model: ports, registers, VRAM, line renderer, sprites, status, time base |
| `clCOM.vb` | COM port, receive thread, line parser, ring buffer, settings file |
| `clVIDEO.vb` | Video recording: interface to `TMS9918AVideo.dll` |
| `frmMain.vb` | Main window: message processing, picture output, status display |
| `frmInit.vb` | Settings dialog (COM port) |
| `UiText.vb` | Language of the user interface |

## 1. Features

- Port state machine of the TMS9918A: address latch, 14-bit address, read-ahead buffer, 4K and 16K
  mode with the 4K DRAM address mapping.
- All screen modes including the undocumented mixed modes, sprites with size, magnification, early
  clock, 4-per-line limit, fifth-sprite and collision flags.
- Line-accurate timing from the sender's time marks: every display line is built from the VRAM and
  register state valid at its time, so changes in the middle of the frame show up where they happen.
- PAL/NTSC detection and frame position tracking from the real VDP's F flag only (interrupts of
  other cartridges do not disturb).
- Comparison of every VRAM read and status read with the real VDP; the first mismatches are logged
  in the status display.
- Reset of the MSX from the PC: Connection > Connect resets the MSX, its RESET message synchronises
  the emulator.
- Video recording of the picture to MP4 (H.264), starting with a reset of the MSX.
- User interface in English or German (System > English / Deutsch).

## 2. Hardware

- An MSX1 with a TMS9918A family VDP (TMS9918A, TMS9928A, TMS9929A).
- The card in this folder: a Raspberry Pi Pico, a GAL22V10 that decodes the VDP ports and produces
  /CSW, /CSR and an address signal for ports 98h/99h, two 74LVC245 that shift the bus signals to
  3.3 V and a 74HCT245 that drives /WAIT and the reset of the MSX. Diodes let the 74HCT245 pull these
  two lines only LOW. The pin assignment is listed in the firmware [README](TMS9918aPiPico/README.md).
- Program the GAL with `pcb/gal/FPGA_IO.jed`.
- The Pico is powered by the MSX through the Schottky diode D103 on VSYS. The Pico can also draw
  power from USB, but D103 keeps the USB port from feeding the MSX.
- While the firmware is not running (power-up, BOOTSEL, flashing), the Pico holds the MSX in reset.
  This is intended: the MSX starts only when the card is ready.
- No hot plug, just like any MSX cartridge: plug in the card only with the MSX switched off.
- To order the board, upload `pcb/gerber/msx_vdp_slot_gerber.zip` to the PCB maker. Check the layers
  in a Gerber viewer (for example the online viewer of the PCB maker) before you order. The parts
  are listed in `pcb/msx_vdp_slot_bom.csv`.

## 3. Firmware

- Easiest way: hold the BOOTSEL button of the Pico while connecting it to the PC, then copy
  `TMS9918aPiPico.ino.uf2` to the drive `RPI-RP2` that appears.
- Or build it yourself with the Arduino-Pico core (earlephilhower), board "Raspberry Pi Pico":

  ```text
  arduino-cli compile --fqbn rp2040:rp2040:rpipico TMS9918aPiPico
  arduino-cli upload  --fqbn rp2040:rp2040:rpipico -p <COM port> TMS9918aPiPico
  ```

The emulator must not have the COM port open while the Pico is flashed.

## 4. Emulator

The program needs Windows 10/11 x64 and the .NET Framework 4.5 or newer (part of Windows). Copy the
folder `bin` anywhere and start `TMS9918A.exe`.

To build it yourself, open `TMS9918A.sln` in Visual Studio 2022 (workloads .NET desktop and C++)
and build, or on the command line:

```text
MSBuild.exe TMS9918A.sln /t:Rebuild /p:Configuration=Release
```

The program is `TMS9918A/bin/Release/TMS9918A.exe`. Before its own build, the emulator project
builds `TMS9918AVideo.dll` (x64) with the shared VIDEOREC library from `../emu/chips` and copies it
next to the program; the C++ intermediate files go to `Build/`.

## 5. Usage

1. Plug the card with the Pico into the MSX and connect the Pico to the PC over USB. While the
   firmware is starting, the Pico holds the MSX in reset.
2. Start `TMS9918A.exe`, choose the Pico's COM port under Connection > Settings.
3. Connection > Connect resets the MSX. As soon as its RESET message arrives, the emulator is
   synchronised and shows the picture.
4. The status display on the right shows the throughput, the VDP registers and tables, the time base
   (PAL/NTSC) and the counters and first entries of VRAM and status mismatches.

The settings (COM port, language and video standard) are stored in `Inifiles/tms9918a_init.txt`
next to the program.

## 6. Video recording

1. Choose the video standard of the MSX under System > Video PAL (50 Hz) or Video NTSC (60 Hz). The
   frame rate of the video follows this choice, not the standard detected from the stream: that one
   is unknown again after every reset of the MSX.
2. Connect to the MSX, then System > Record video... and choose the file. Recording is possible only
   while connected.
3. Right after the start the emulator resets the MSX. The video begins with its RESET message, so
   every recording shows the machine from power-on.
4. System > Stop video, Disconnect or closing the program finishes the file. The status bar shows
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
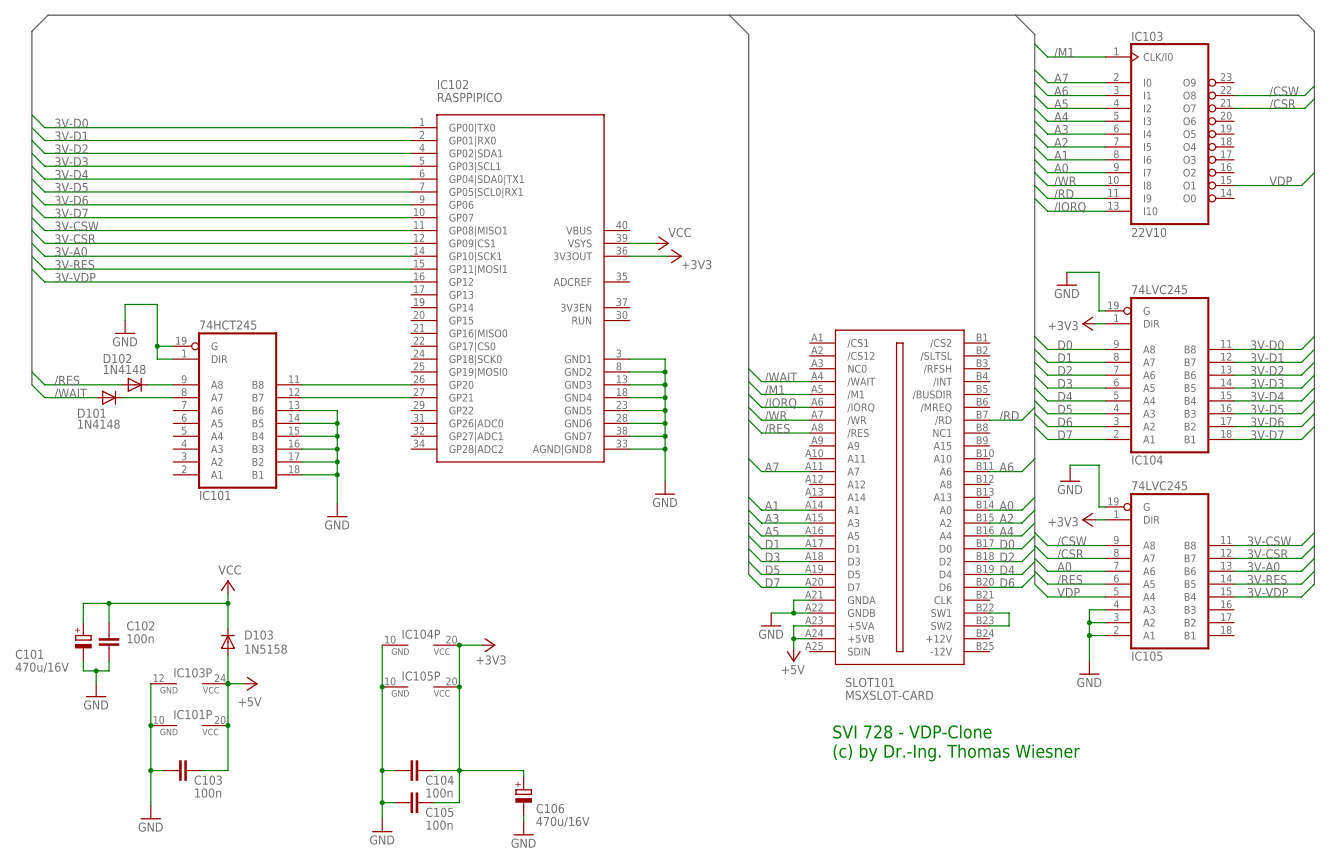
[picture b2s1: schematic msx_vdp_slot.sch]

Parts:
C101, C106: 470u/16V; E3,5-8
C102, C103, C104, C105: 100n; C025-025X050
D101, D102: 1N4148; DO35-10
D103: 1N5158; DO41-10
IC101: 74HCT245; DIL20
IC102: RASPPIPICO
IC103: 22V10; DIL24-3
IC104, IC105: 74LVC245; DIL20
SLOT101: MSXSLOT-CARD; MSXCARD

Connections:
3V-A0: IC102.14 (GP10|SCK1), IC105.13 (B6)
3V-CSR: IC102.12 (GP09|CS1), IC105.12 (B7)
3V-CSW: IC102.11 (GP08|MISO1), IC105.11 (B8)
3V-D0: IC102.1 (GP00|TX0), IC104.11 (B8)
3V-D1: IC102.2 (GP01|RX0), IC104.12 (B7)
3V-D2: IC102.4 (GP02|SDA1), IC104.13 (B6)
3V-D3: IC102.5 (GP03|SCL1), IC104.14 (B5)
3V-D4: IC102.6 (GP04|SDA0|TX1), IC104.15 (B4)
3V-D5: IC102.7 (GP05|SCL0|RX1), IC104.16 (B3)
3V-D6: IC102.9 (GP06), IC104.17 (B2)
3V-D7: IC102.10 (GP07), IC104.18 (B1)
3V-RES: IC102.15 (GP11|MOSI1), IC105.14 (B5)
3V-VDP: IC102.16 (GP12), IC105.15 (B4)
+3V3: C104.1, C105.1, C106.+, IC102.36 (3V3OUT), IC104.1 (DIR), IC104.20 (VCC), IC105.1 (DIR), IC105.20 (VCC)
+5V: C103.1, D103.A, IC101.20 (VCC), IC103.24 (VCC), SLOT101.A23 (+5VA), SLOT101.A24 (+5VB)
/CSR: IC103.21 (O7), IC105.8 (A7)
/CSW: IC103.22 (O8), IC105.9 (A8)
/IORQ: IC103.13 (I10), SLOT101.A6 (/IORQ)
/M1: IC103.1 (CLK/I0), SLOT101.A5 (/M1)
/RD: IC103.11 (I9), SLOT101.B7 (/RD)
/RES: D102.A, IC105.6 (A5), SLOT101.A8 (/RES)
/WAIT: D101.A, SLOT101.A4 (/WAIT)
/WR: IC103.10 (I8), SLOT101.A7 (/WR)
A0: IC103.9 (I7), IC105.7 (A6), SLOT101.B14 (A0)
A1: IC103.8 (I6), SLOT101.A14 (A1)
A2: IC103.7 (I5), SLOT101.B15 (A2)
A3: IC103.6 (I4), SLOT101.A15 (A3)
A4: IC103.5 (I3), SLOT101.B16 (A4)
A5: IC103.4 (I2), SLOT101.A16 (A5)
A6: IC103.3 (I1), SLOT101.B11 (A6)
A7: IC103.2 (I0), SLOT101.A11 (A7)
ADCREF: IC102.35 (ADCREF)
D0: IC104.9 (A8), SLOT101.B17 (D0)
D1: IC104.8 (A7), SLOT101.A17 (D1)
D2: IC104.7 (A6), SLOT101.B18 (D2)
D3: IC104.6 (A5), SLOT101.A18 (D3)
D4: IC104.5 (A4), SLOT101.B19 (D4)
D5: IC104.4 (A3), SLOT101.A19 (D5)
D6: IC104.3 (A2), SLOT101.B20 (D6)
D7: IC104.2 (A1), SLOT101.A20 (D7)
GND: C101.-, C102.2, C103.2, C104.2, C105.2, C106.-, IC101.1 (DIR), IC101.10 (GND), IC101.13 (B6), IC101.14 (B5), IC101.15 (B4), IC101.16 (B3), IC101.17 (B2), IC101.18 (B1), IC101.19 (G), IC102.3 (GND1), IC102.8 (GND2), IC102.13 (GND3), IC102.18 (GND4), IC102.23 (GND5), IC102.28 (GND6), IC102.33 (AGND|GND8), IC102.38 (GND7), IC103.12 (GND), IC104.10 (GND), IC104.19 (G), IC105.2 (A1), IC105.3 (A2), IC105.4 (A3), IC105.10 (GND), IC105.19 (G), SLOT101.A21 (GNDA), SLOT101.A22 (GNDB)
unnamed: D102.C, IC101.9 (A8)
unnamed: D101.C, IC101.8 (A7)
unnamed: IC101.12 (B7), IC102.27 (GP21)
unnamed: IC101.11 (B8), IC102.26 (GP20)
unnamed: SLOT101.B22 (SW1), SLOT101.B23 (SW2)
VBUS: IC102.40 (VBUS)
VCC: C101.+, C102.1, D103.C, IC102.39 (VSYS)
VDP: IC103.15 (O1), IC105.5 (A4)

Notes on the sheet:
SVI 728 - VDP-Clone (c) by Dr.-Ing. Thomas Wiesner

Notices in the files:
tms9918a/TMS9918aPiPico/TMS9918aPiPico.ino:
MSX (c) 2026 by Dr.-Ing. Thomas Wiesner
README.md:
9. License:
Except where explicitly stated otherwise, this repository is licensed as follows (details in [LICENSE.txt](LICENSE.txt)):
Content | License
Software: source code, build scripts, firmware | [MIT](LICENSE.txt)
Hardware designs: schematics, PCB layouts, Gerber and drill files, bills of materials, GAL equations, 3D models of enclosures (FreeCAD) | [CERN-OHL-S-2.0](LICENSE-CERN-OHL-S-2.0.txt)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
